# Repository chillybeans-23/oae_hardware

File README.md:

# OAE Hardware

probe_tip branch includes probe nozzle PCB, as well as chassis CAD

## Bill of Materials

[TODO]
* Speakers
* Microphone
* 34AWG magnet wire
* 0402? components
* PCBs
* EEPROM chips
* HDMI cable
* Assorted heatshrink tubing
* 

## Assembly Instructions

The optimal location to assemble the probe is in the EE Proto Room. Here, you can find the necessary equipment to assemble the probe:

* Weller soldering station, with fine point iron tip
* Fine gauge lead-free solder wire
* No-clean flux
* Helping hands with silicone, with rubber alligator clip covers
* Silicone soldering pad
* Mounting putty (poster putty)
* Hotplate
* Tweezers
* Wire strippers
* Exacto knife
* Multimeter

### Step 1: Assemble the PCB

The nozzle PCB contains the Microchip 24LC32A I2C compatible serial EEPROM, its auxiliary components, and pads to solder HDMI and magnet wire to. To assemble the components before hand-soldering the magnet wire and HDMI cable, follow these instructions, and refer to Bradley Minch for use of his hotplate or expertise:

**Instructions for solder application**

[TODO] assemble another PCB and take pictures for each step

1. Lay PCB on silicone or other flat surface with IC/component side upwards
2. Lay stencil over PCB, ensuring the component pads line up
3. Carefully align stencil on top of PCB and hold down firmly
4. Applying tension, tape opposite corners of stencil to the work surface
5. Repeat for the other two corners of the stencil
6. Ensure the component pads still line up with the stencil cutouts, and the PCB is held securely in place
7. Mix the solder paste evenly
8. Apply a rice grain size amount of solder paste to the stencil next to the cutouts
9. Applying moderate pressure with the squeegee at a 30 degree angle with the surface, drag the solder paste along the stencil into the cutouts
10. Drag the solder paste the other way
11. Repeat 1-2 times until all the cutouts are full of solder paste
12. Using the squeegee, scrape the excess solder paste off the stencil
13. Scrape the excess solder paste off the squeegee back into the container
14. Untape the stencil from the work surface
15. Ensure there is an even layer of solder paste on the pads of the PCB
16. Using isopropyl alcohol and a Kimwipe, clean the squeegee and stencil

**Instructions for Populating the PCB**

1. Refer to the interactive Bill of Materials (BOM) for component values and locations [TODO]
2. Cut one 1uF capacitor and two 2k resistors off their respective tapes
3. Use angled tweezers to place the components
    * Getting one tweezer prong slightly sticky and just using that prong to place is better than pinching the components
    * Place hand on table close to PCB for stability
    * The specified capacitors and resistors have no polarity and can be placed with any side up, as long as the component lays flat along the PCB

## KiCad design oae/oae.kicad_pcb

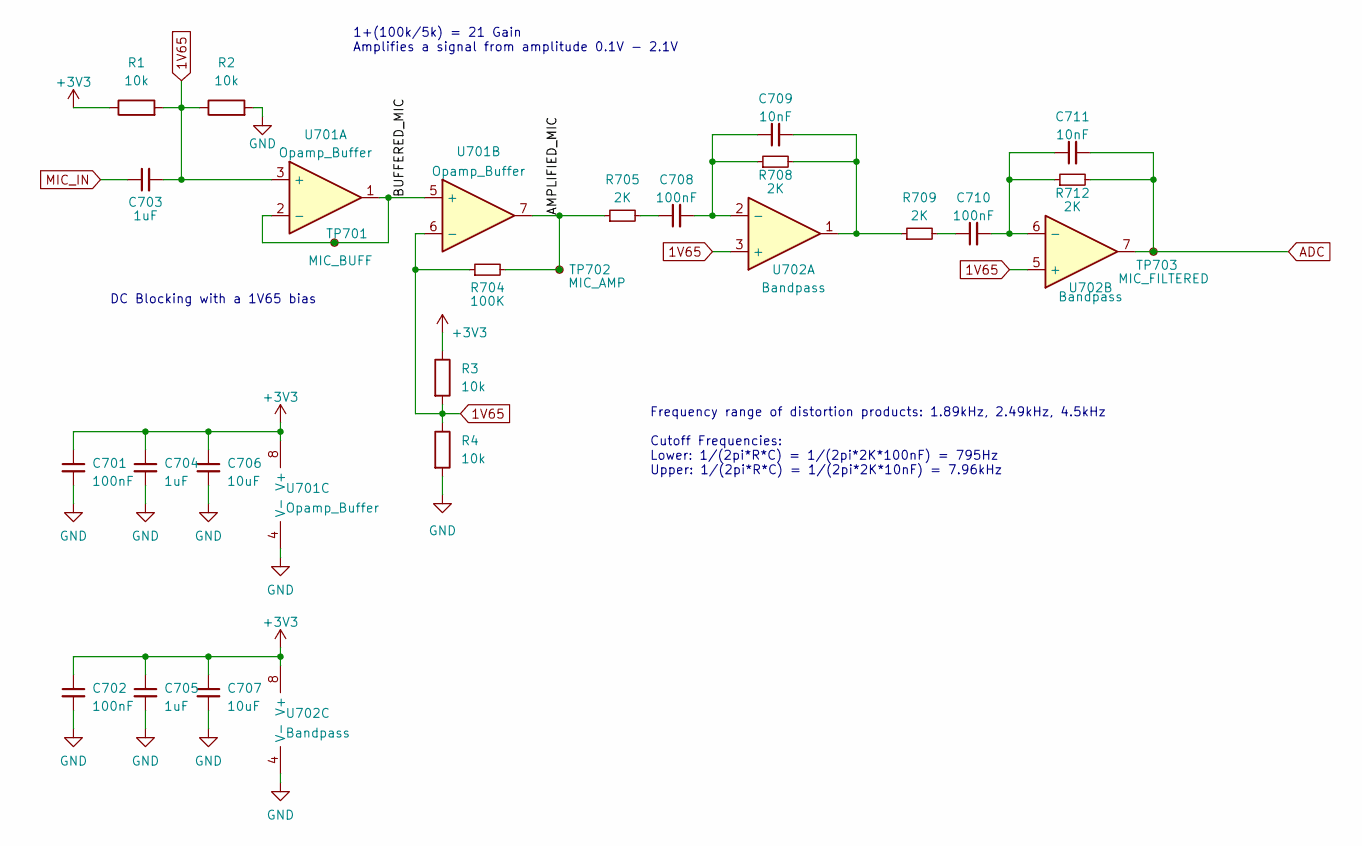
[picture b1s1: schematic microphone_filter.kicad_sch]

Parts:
C701, C702: 100nF; C_0603_1608Metric
C703: 1uF; C_1206_3216Metric_Pad1.33x1.80mm_HandSolder
C704, C705: 1uF; C_0603_1608Metric
C706, C707: 10uF; C_0603_1608Metric
C708, C710: 100nF; C_1206_3216Metric
C709, C711: 10nF; C_0603_1608Metric
R1, R2, R3, R4: 10k; R_0603_1608Metric
R704: 100K; R_0603_1608Metric_Pad0.98x0.95mm_HandSolder
R705, R708, R709, R712: 2K; R_0603_1608Metric_Pad0.98x0.95mm_HandSolder
TP701: MIC_BUFF; TestPoint_Pad_D2.5mm
TP702: MIC_AMP; TestPoint_Pad_D2.5mm
TP703: MIC_FILTERED; TestPoint_Pad_D2.5mm
U1: PCM1862DBT; C_0603_1608Metric
U701: Opamp_Buffer; SOIC127P599X175-8N; Digikey MCP6022-I/SN-ND
U702: Bandpass; SOIC127P599X175-8N; Digikey MCP6022-I/SN-ND

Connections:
/Microphone Filters and Amp/AMPLIFIED_MIC: R704.2, R705.1, TP702.1, U701.7
/Microphone Filters and Amp/BUFFERED_MIC: TP701.1, U701.1, U701.2 (-), U701.5 (+)
ADC: C711.2, R712.2, TP703.1, U702.7; also elsewhere on the board
MIC_IN: C703.1; also elsewhere on the board
unnamed: C708.1, R705.2
unnamed: C709.2, R708.2, R709.1, U702.1
unnamed: C710.1, R709.2
unnamed: C708.2, C709.1, R708.1, U702.2 (-)
unnamed: C710.2, C711.1, R712.1, U702.6 (-)

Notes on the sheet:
1+(100k/5k) = 21 Gain Amplifies a signal from amplitude 0.1V - 2.1V
DC Blocking with a 1V65 bias
Frequency range of distortion products: 1.89kHz, 2.49kHz, 4.5kHz Cutoff Frequencies: Lower: 1/(2pi*R*C) = 1/(2pi*2K*100nF) = 795Hz Upper: 1/(2pi*R*C) = 1/(2pi*2K*10nF) = 7.96kHz

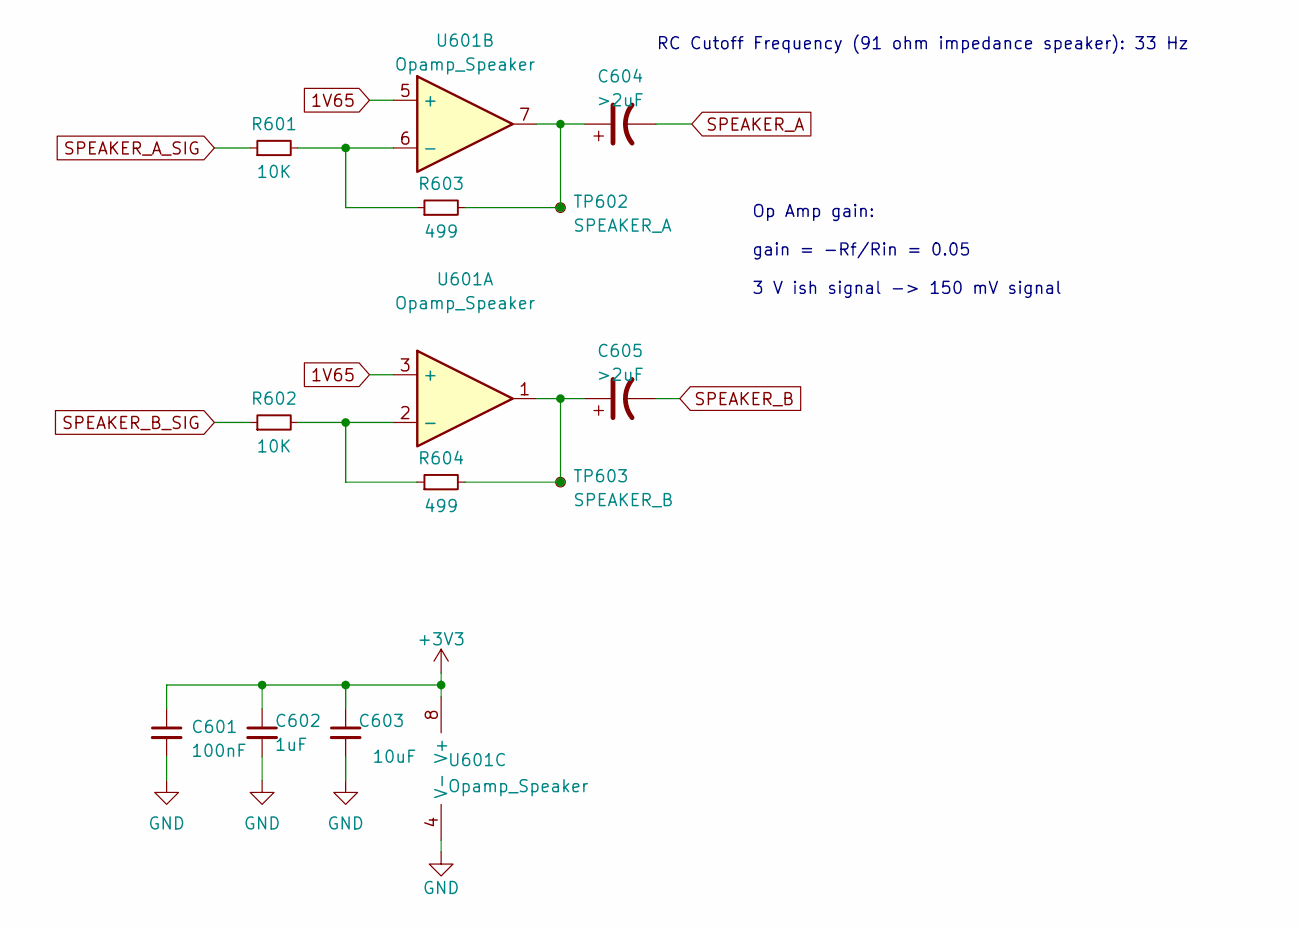
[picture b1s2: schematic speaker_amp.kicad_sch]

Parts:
C601: 100nF; C_0603_1608Metric
C602: 1uF; C_0603_1608Metric
C603: 10uF; C_0603_1608Metric
C604, C605: >2uF; C_0805_2012Metric_Pad1.18x1.45mm_HandSolder
R601, R602: 10K; R_0603_1608Metric_Pad0.98x0.95mm_HandSolder
R603, R604: 499; R_0603_1608Metric_Pad0.98x0.95mm_HandSolder
TP602: SPEAKER_A; TestPoint_Pad_D2.5mm
TP603: SPEAKER_B; TestPoint_Pad_D2.5mm
U601: Opamp_Speaker; SOIC127P599X175-8N; Digikey MCP6022-I/SN-ND

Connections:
unnamed: C604.1, R603.2, TP602.1, U601.7
unnamed: C605.1, R604.2, TP603.1, U601.1
unnamed: R602.2, R604.1, U601.2 (-)
unnamed: R601.2, R603.1, U601.6 (-)
SPEAKER_A: C604.2; also elsewhere on the board
SPEAKER_A_SIG: R601.1; also elsewhere on the board
SPEAKER_B: C605.2; also elsewhere on the board
SPEAKER_B_SIG: R602.1; also elsewhere on the board

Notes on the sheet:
Op Amp gain: gain = -Rf/Rin = 0.05 3 V ish signal -> 150 mV signal
RC Cutoff Frequency (91 ohm impedance speaker): 33 Hz

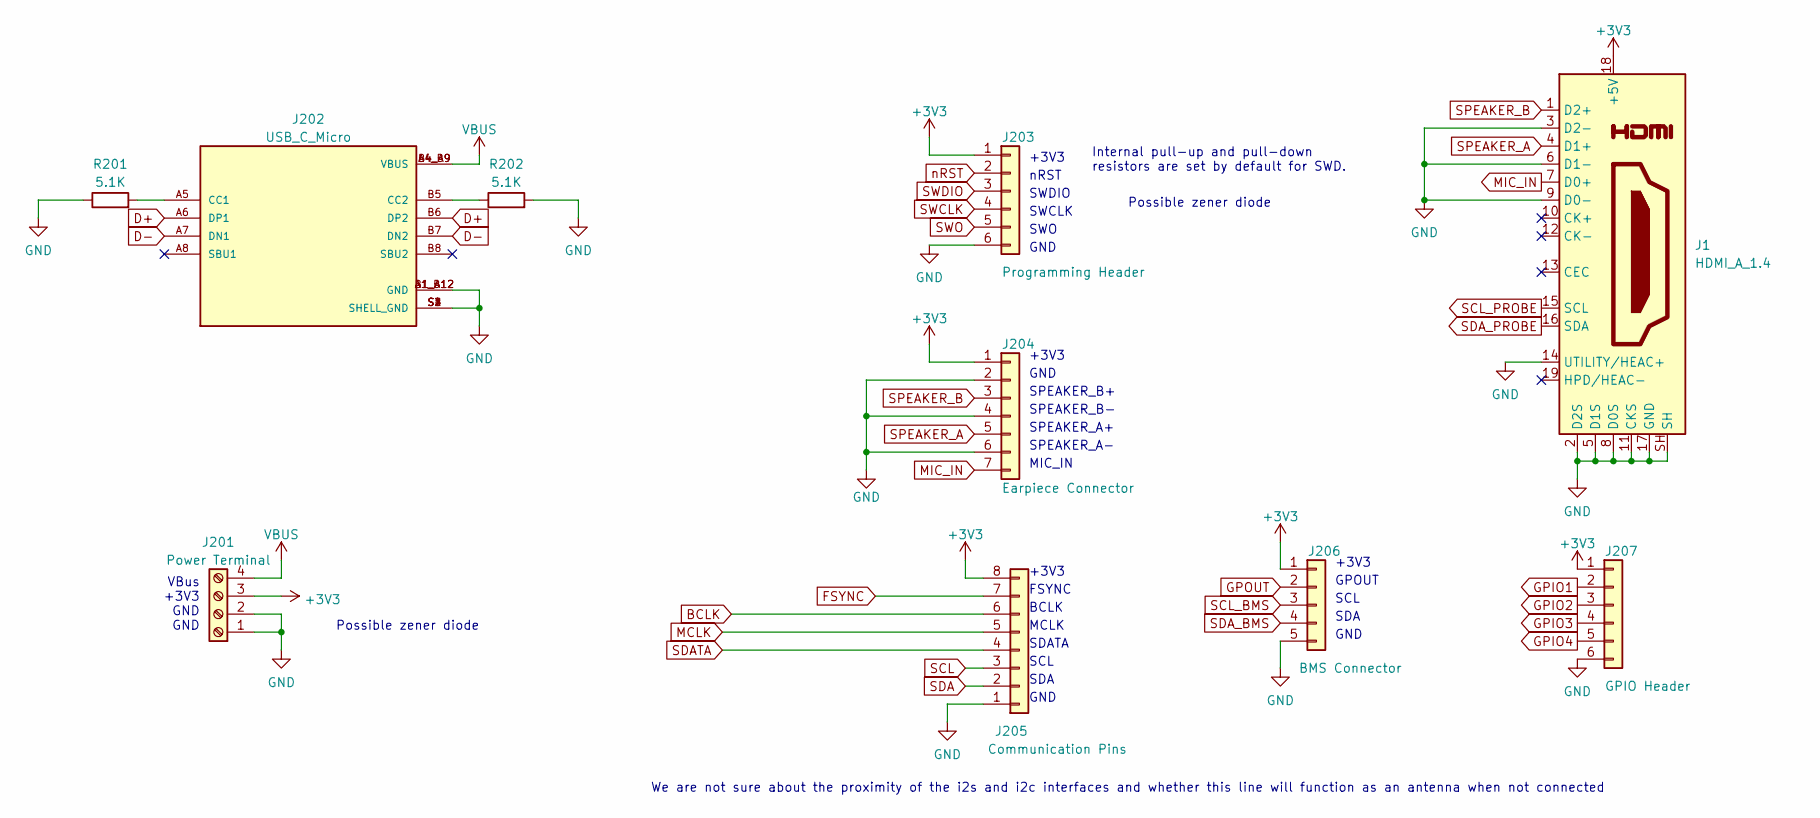
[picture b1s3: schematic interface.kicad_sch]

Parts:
J1: HDMI_A_1.4; HDMI_A_Molex_208658-1001_Horizontal
J201: Power Terminal; PinHeader_1x04_P2.54mm_Vertical
J202: USB_C_Micro; GCT_USB4105-GF-A; PARTREV A3
J203: Programming Header; PinHeader_1x06_P2.54mm_Vertical
J204: Earpiece Connector; PinHeader_1x07_P2.54mm_Vertical
J205: Communication Pins; PinHeader_1x08_P2.54mm_Vertical
J206: BMS Connector; PinHeader_1x05_P2.54mm_Vertical
J207: GPIO Header; PinHeader_1x06_P2.54mm_Vertical
R201, R202: 5.1K; R_0603_1608Metric_Pad0.98x0.95mm_HandSolder

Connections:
BCLK: J205.6; also elsewhere on the board
D+: J202.A6 (DP1), J202.B6 (DP2); also elsewhere on the board
D-: J202.A7 (DN1), J202.B7 (DN2); also elsewhere on the board
FSYNC: J205.7; also elsewhere on the board
GPIO1: J207.2; also elsewhere on the board
GPIO2: J207.3; also elsewhere on the board
GPIO3: J207.4; also elsewhere on the board
GPIO4: J207.5; also elsewhere on the board
GPOUT: J206.2; also elsewhere on the board
MCLK: J205.5; also elsewhere on the board
MIC_IN: J1.7 (D0+), J204.7; also elsewhere on the board
unnamed: J202.A5 (CC1), R201.2
unnamed: J202.B5 (CC2), R202.1
SCL: J205.3; also elsewhere on the board
SCL_BMS: J206.3; also elsewhere on the board
SCL_PROBE: J1.15 (SCL); also elsewhere on the board
SDA: J205.2; also elsewhere on the board
SDATA: J205.4; also elsewhere on the board
SDA_BMS: J206.4; also elsewhere on the board
SDA_PROBE: J1.16 (SDA); also elsewhere on the board
SPEAKER_A: J1.4 (D1+), J204.5; also elsewhere on the board
SPEAKER_B: J1.1 (D2+), J204.3; also elsewhere on the board
SWCLK: J203.4; also elsewhere on the board
SWDIO: J203.3; also elsewhere on the board
SWO: J203.5; also elsewhere on the board
VBUS: J201.4, J202.A4_B9 (VBUS), J202.B4_A9 (VBUS); also elsewhere on the board
nRST: J203.2; also elsewhere on the board

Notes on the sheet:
SPEAKER_B-
SWO
MIC_IN
GND
VBus +3V3 GND GND
MCLK
nRST
SPEAKER_A+
+3V3
FSYNC
SCL
GPOUT
Internal pull-up and pull-down resistors are set by default for SWD.
Possible zener diode
We are not sure about the proximity of the i2s and i2c interfaces and whether this line will function as an antenna when not connected
SWCLK
SDA
SPEAKER_A-
SWDIO
BCLK
SPEAKER_B+
SDATA
SCL

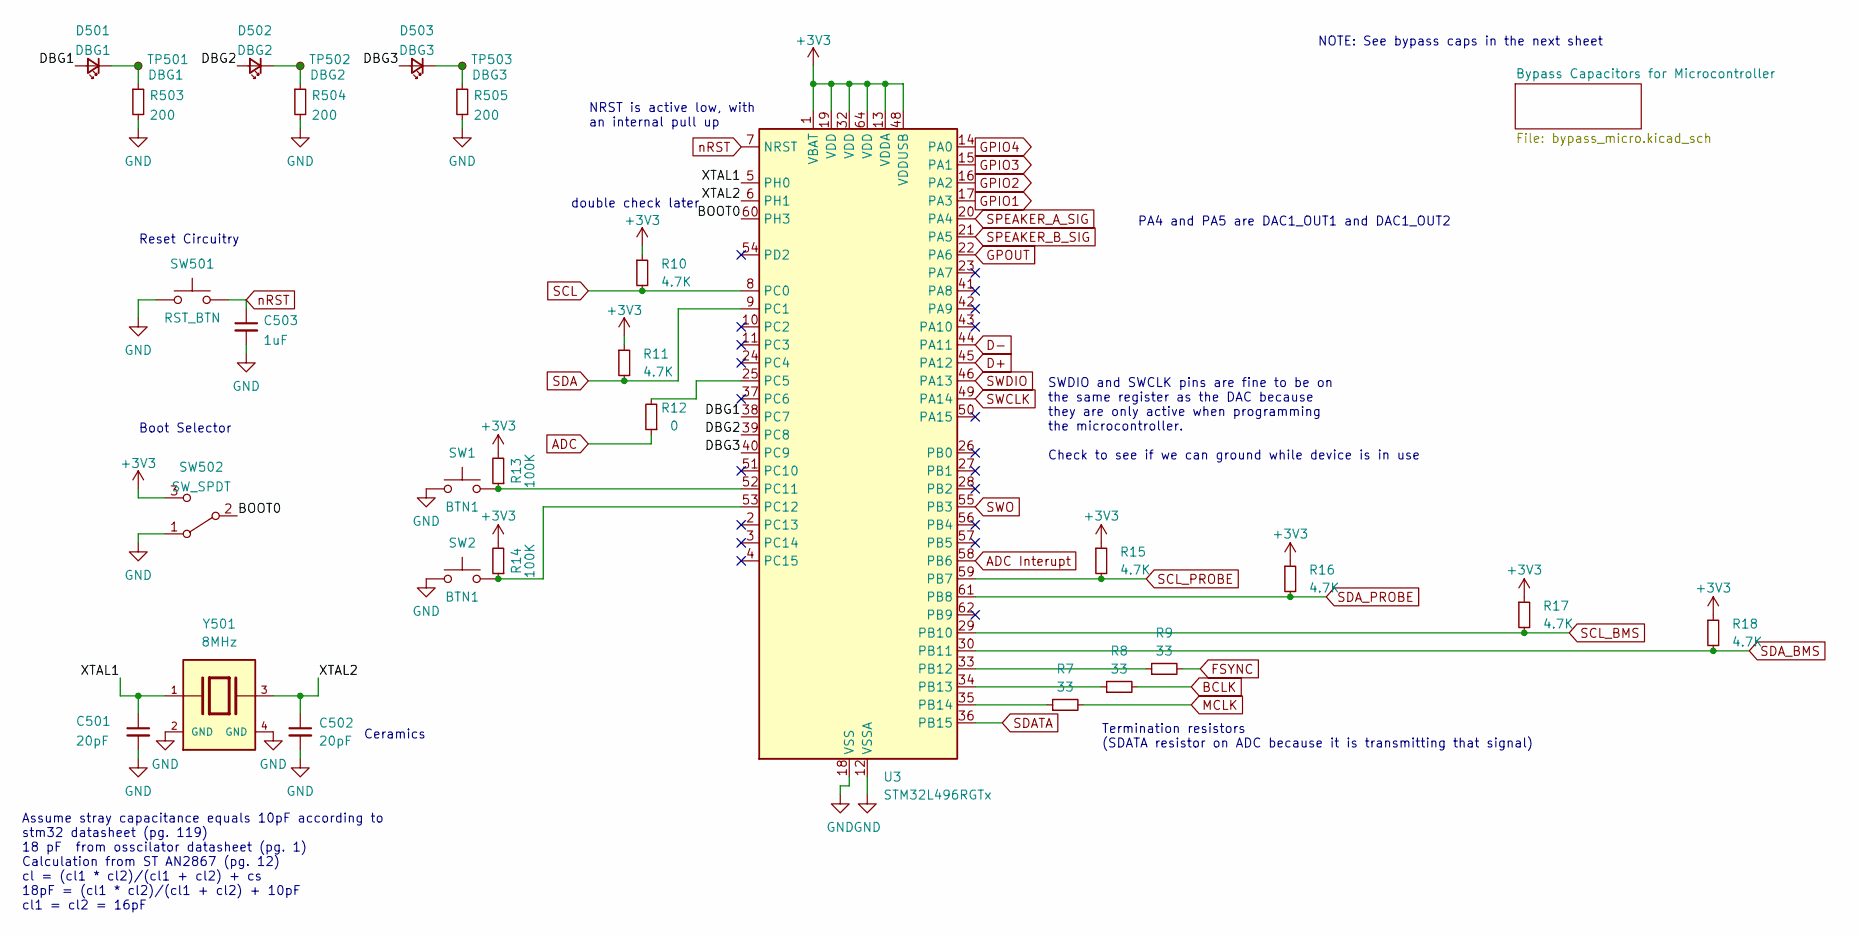
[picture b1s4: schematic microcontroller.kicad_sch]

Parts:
C501, C502: 20pF; C_0603_1608Metric
C503: 1uF; C_0603_1608Metric
D501: DBG1; LED_0603_1608Metric
D502: DBG2; LED_0603_1608Metric
D503: DBG3; LED_0603_1608Metric
R7, R8, R9: 33; R_0603_1608Metric_Pad0.98x0.95mm_HandSolder
R10, R11, R15, R16, R17, R18: 4.7K; R_0603_1608Metric_Pad0.98x0.95mm_HandSolder
R12: 0; R_0603_1608Metric_Pad0.98x0.95mm_HandSolder
R13, R14: 100K; R_0603_1608Metric_Pad0.98x0.95mm_HandSolder
R503, R504, R505: 200; R_0603_1608Metric_Pad0.98x0.95mm_HandSolder
SW1, SW2: BTN1; SW_SPST_EVPBF; DigiKey P19749DKR-ND
SW501: RST_BTN; SW_SPST_EVPBF; DigiKey P19749DKR-ND
SW502: SW_SPDT; PinHeader_1x03_P2.54mm_Vertical
TP501: DBG1; TestPoint_Pad_1.5x1.5mm
TP502: DBG2; TestPoint_Pad_1.5x1.5mm
TP503: DBG3; TestPoint_Pad_1.5x1.5mm
U3: STM32L496RGTx; LQFP-64_10x10mm_P0.5mm
Y501: 8MHz; XTAL_ABMM2-8.000MHZ-E2-T; PARTREV 01.18.13

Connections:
/Microcontroller/BOOT0: SW502.2 (B), U3.60 (PH3)
/Microcontroller/DBG1: D501.2 (A), U3.38 (PC7)
/Microcontroller/DBG2: D502.2 (A), U3.39 (PC8)
/Microcontroller/DBG3: D503.2 (A), U3.40 (PC9)
/Microcontroller/XTAL1: C501.1, U3.5 (PH0), Y501.1
/Microcontroller/XTAL2: C502.1, U3.6 (PH1), Y501.3
ADC: R12.1; also elsewhere on the board
ADC Interupt: U3.58 (PB6); also elsewhere on the board
BCLK: R8.2; also elsewhere on the board
D+: U3.45 (PA12); also elsewhere on the board
D-: U3.44 (PA11); also elsewhere on the board
FSYNC: R9.2; also elsewhere on the board
GPIO1: U3.17 (PA3); also elsewhere on the board
GPIO2: U3.16 (PA2); also elsewhere on the board
GPIO3: U3.15 (PA1); also elsewhere on the board
GPIO4: U3.14 (PA0); also elsewhere on the board
GPOUT: U3.22 (PA6); also elsewhere on the board
MCLK: R7.2; also elsewhere on the board
unnamed: D501.1 (K), R503.1, TP501.1
unnamed: D502.1 (K), R504.1, TP502.1
unnamed: D503.1 (K), R505.1, TP503.1
unnamed: R9.1, U3.33 (PB12)
unnamed: R8.1, U3.34 (PB13)
unnamed: R7.1, U3.35 (PB14)
unnamed: R12.2, U3.25 (PC5)
unnamed: R13.1, SW1.2, U3.52 (PC11)
unnamed: R14.1, SW2.2, U3.53 (PC12)
SCL: R10.2, U3.8 (PC0); also elsewhere on the board
SCL_BMS: R17.2, U3.29 (PB10); also elsewhere on the board
SCL_PROBE: R15.2, U3.59 (PB7); also elsewhere on the board
SDA: R11.2, U3.9 (PC1); also elsewhere on the board
SDATA: U3.36 (PB15); also elsewhere on the board
SDA_BMS: R18.2, U3.30 (PB11); also elsewhere on the board
SDA_PROBE: R16.2, U3.61 (PB8); also elsewhere on the board
SPEAKER_A_SIG: U3.20 (PA4); also elsewhere on the board
SPEAKER_B_SIG: U3.21 (PA5); also elsewhere on the board
SWCLK: U3.49 (PA14); also elsewhere on the board
SWDIO: U3.46 (PA13); also elsewhere on the board
SWO: U3.55 (PB3); also elsewhere on the board
nRST: C503.1, SW501.2, U3.7 (NRST); also elsewhere on the board

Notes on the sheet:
Ceramics
Termination resistors (SDATA resistor on ADC because it is transmitting that signal)
Reset Circuitry
Boot Selector
NRST is active low, with an internal pull up
Assume stray capacitance equals 10pF according to stm32 datasheet (pg. 119) 18 pF from osscilator datasheet (pg. 1) Calculation from ST AN2867 (pg. 12) cl = (cl1 * cl2)/(cl1 + cl2) + cs 18pF = (cl1 * cl2)/(cl1 + cl2) + 10pF cl1 = cl2 = 16pF
double check later
NOTE: See bypass caps in the next sheet
PA4 and PA5 are DAC1_OUT1 and DAC1_OUT2
SWDIO and SWCLK pins are fine to be on the same register as the DAC because they are only active when programming the microcontroller. Check to see if we can ground while device is in use

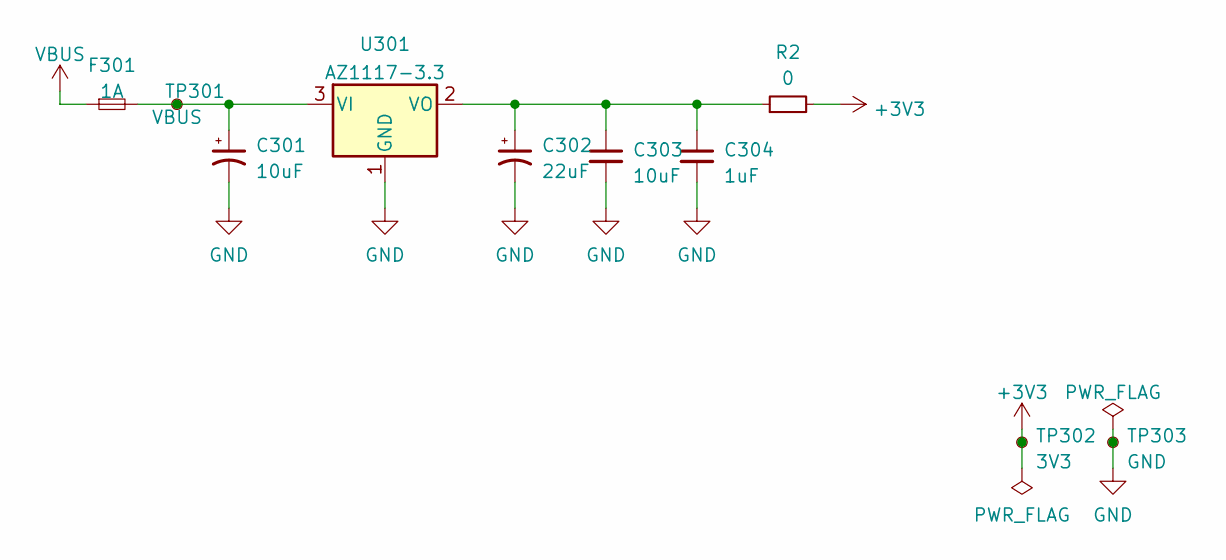
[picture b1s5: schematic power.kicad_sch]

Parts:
C301, C303: 10uF; C_0603_1608Metric
C302: 22uF; C_0603_1608Metric
C304: 1uF; C_0603_1608Metric
F301: 1A; Fuse_1206_3216Metric; DigiKey 507-1806-6-ND
R2: 0; R_0603_1608Metric_Pad0.98x0.95mm_HandSolder
TP301: VBUS; TestPoint_Pad_D2.5mm
TP302: 3V3; TestPoint_Pad_D2.5mm
TP303: GND; TestPoint_Pad_D2.5mm
U301: AZ1117-3.3; TO-252-3_TabPin2; DigiKey AZ1117CD-3.3TRG1DIDKR-ND

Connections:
unnamed: C301.1, F301.2, TP301.1, U301.3 (VI)
VBUS: F301.1; also elsewhere on the board

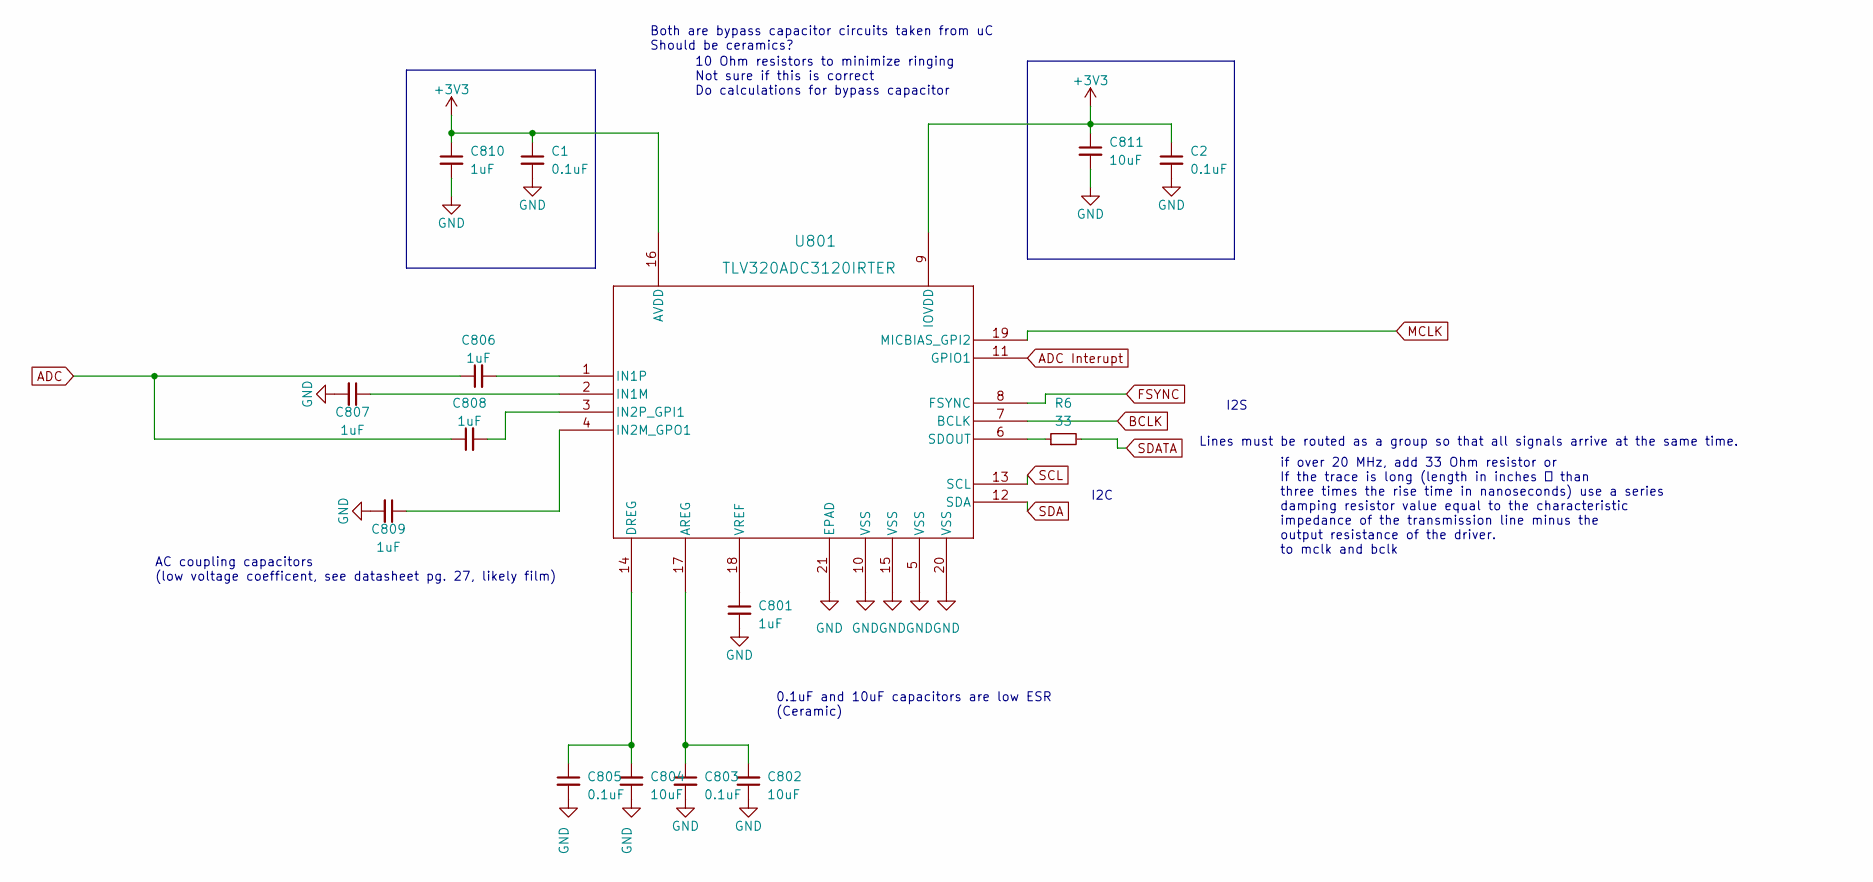
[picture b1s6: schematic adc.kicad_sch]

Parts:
C1, C2, C803, C805: 0.1uF; C_0603_1608Metric
C801, C810: 1uF; C_0603_1608Metric
C802, C804, C811: 10uF; C_0603_1608Metric
C806, C807, C808, C809: 1uF; C_1206_3216Metric_Pad1.33x1.80mm_HandSolder
R6: 33; R_0603_1608Metric_Pad0.98x0.95mm_HandSolder
U801: TLV320ADC3120IRTER; WQFN20_RTE_TEX

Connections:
ADC: C806.1, C808.1; also elsewhere on the board
ADC Interupt: U801.11 (GPIO1); also elsewhere on the board
BCLK: U801.7 (BCLK); also elsewhere on the board
FSYNC: U801.8 (FSYNC); also elsewhere on the board
MCLK: U801.19 (MICBIAS_GPI2); also elsewhere on the board
unnamed: C802.2, C803.1, U801.17 (AREG)
unnamed: C804.2, C805.1, U801.14 (DREG)
unnamed: C807.1, U801.2 (IN1M)
unnamed: C806.2, U801.1 (IN1P)
unnamed: C809.1, U801.4 (IN2M_GPO1)
unnamed: C808.2, U801.3 (IN2P_GPI1)
unnamed: R6.1, U801.6 (SDOUT)
unnamed: C801.1, U801.18 (VREF)
SCL: U801.13 (SCL); also elsewhere on the board
SDA: U801.12 (SDA); also elsewhere on the board
SDATA: R6.2; also elsewhere on the board

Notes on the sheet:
AC coupling capacitors (low voltage coefficent, see datasheet pg. 27, likely film)
I2C
10 Ohm resistors to minimize ringing Not sure if this is correct Do calculations for bypass capacitor
0.1uF and 10uF capacitors are low ESR (Ceramic)
if over 20 MHz, add 33 Ohm resistor or If the trace is long (length in inches  than three times the rise time in nanoseconds) use a series damping resistor value equal to the characteristic impedance of the transmission line minus the output resistance of the driver. to mclk and bclk
I2S
Lines must be routed as a group so that all signals arrive at the same time.
Both are bypass capacitor circuits taken from uC Should be ceramics?

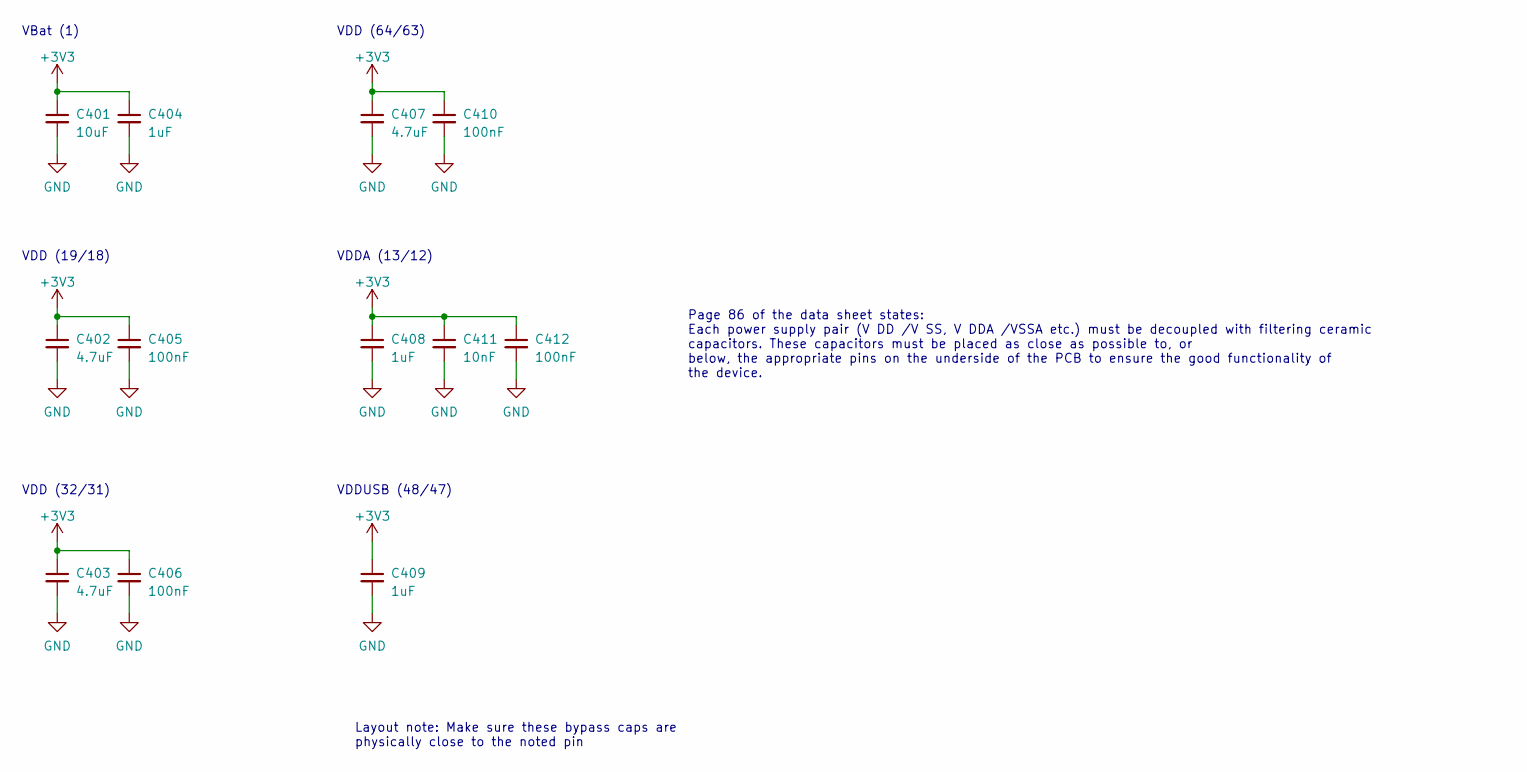
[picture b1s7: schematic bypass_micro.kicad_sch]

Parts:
C401: 10uF; C_0603_1608Metric
C402, C403, C407: 4.7uF; C_0603_1608Metric
C404, C408, C409: 1uF; C_0603_1608Metric
C405, C406, C410, C412: 100nF; C_0603_1608Metric
C411: 10nF; C_0603_1608Metric

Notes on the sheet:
VBat (1)
VDD (64/63)
Layout note: Make sure these bypass caps are physically close to the noted pin
VDD (32/31)
VDD (19/18)
VDDA (13/12)
Page 86 of the data sheet states: Each power supply pair (V DD /V SS, V DDA /VSSA etc.) must be decoupled with filtering ceramic capacitors. These capacitors must be placed as close as possible to, or below, the appropriate pins on the underside of the PCB to ensure the good functionality of the de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
VDDUSB (48/47)

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
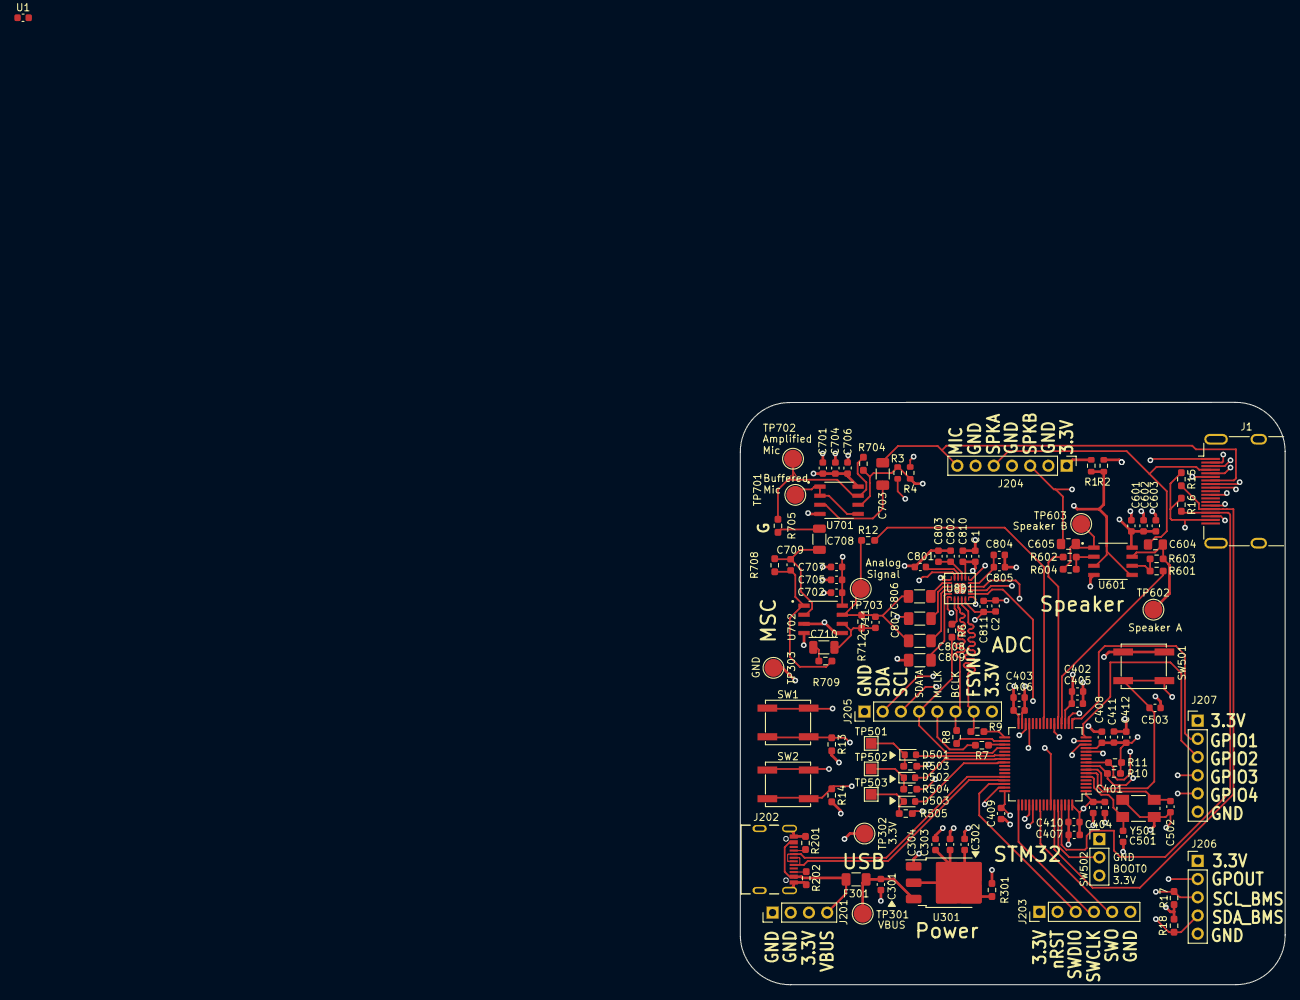
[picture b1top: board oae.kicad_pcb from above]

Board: 4 copper layers, 76.0 x 81.2 mm, 115 parts (0 on the bottom side), 70 nets.

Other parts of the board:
R301: 0; R_0603_1608Metric_Pad0.98x0.95mm_HandSolder

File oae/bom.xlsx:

Id | Designator | Footprint | Quantity | Comment | Supplier and ref
1 | TP302 | TestPoint_Pad_D2.5mm | 1 | 3V3
2 | C304,C704,C404,C408,C801,C409,C503,C810,C705,C602 | C_0603_1608Metric | 10 | 1uF
3 | C702,C601,C405,C406,C410,C701,C412 | C_0603_1608Metric | 7 | 100nF
4 | J206 | PinHeader_1x05_P2.54mm_Vertical | 1 | BMS Connector
5 | C804,C301,C706,C811,C603,C303,C802,C707,C401 | C_0603_1608Metric | 9 | 10uF
6 | TP701 | TestPoint_Pad_D2.5mm | 1 | MIC_BUFF
7 | R504,R503,R505 | R_0603_1608Metric_Pad0.98x0.95mm_HandSolder | 3 | 200
8 | R201,R202 | R_0603_1608Metric_Pad0.98x0.95mm_HandSolder | 2 | 5.1K
9 | J207 | PinHeader_1x06_P2.54mm_Vertical | 1 | GPIO Header
10 | R604,R603 | R_0603_1608Metric_Pad0.98x0.95mm_HandSolder | 2 | 499
11 | C605,C604 | C_0805_2012Metric_Pad1.18x1.45mm_HandSolder | 2 | >2uF
12 | R708,R709,R705,R712 | R_0603_1608Metric_Pad0.98x0.95mm_HandSolder | 4 | 2K
13 | TP502 | TestPoint_Pad_1.5x1.5mm | 1 | DBG2
14 | C708,C710 | C_0805_2012Metric_Pad1.18x1.45mm_HandSolder | 2 | 100nF
15 | RN3,RN1,RN2 | R_Array_Convex_2x0603 | 3 | 10K
16 | C2,C803,C805,C1 | C_0603_1608Metric | 4 | 0.1uF
17 | TP603 | TestPoint_Pad_D2.5mm | 1 | SPEAKER_B
18 | C502,C501 | C_0603_1608Metric | 2 | 16pF
19 | R301,R12 | R_0603_1608Metric_Pad0.98x0.95mm_HandSolder | 2 | 0
20 | TP303 | TestPoint_Pad_D2.5mm | 1 | GND
21 | R17,R10,R15,R16,R11,R18 | R_0603_1608Metric_Pad0.98x0.95mm_HandSolder | 6 | 4.7K
22 | J202 | GCT_USB4105-GF-A | 1 | USB_C_Micro
23 | J201 | PinHeader_1x04_P2.54mm_Vertical | 1 | Power Terminal
24 | SW2,SW1 | SW_SPST_EVPBF | 2 | BTN1
25 | TP501 | TestPoint_Pad_1.5x1.5mm | 1 | DBG1
26 | R704,R14,R13 | R_0603_1608Metric_Pad0.98x0.95mm_HandSolder | 3 | 100K
27 | F301 | Fuse_1206_3216Metric | 1 | 1A
28 | J204 | PinHeader_1x07_P2.54mm_Vertical | 1 | Earpiece Connector
29 | D503 | LED_0603_1608Metric | 1 | DBG3
30 | TP301 | TestPoint_Pad_D2.5mm | 1 | VBUS
31 | C809,C703,C806,C808,C807 | C_1206_3216Metric_Pad1.33x1.80mm_HandSolder | 5 | 1uF
32 | R9,R7,R8,R6 | R_0603_1608Metric_Pad0.98x0.95mm_HandSolder | 4 | 33
33 | SW501 | SW_SPST_EVPBF | 1 | RST_BTN
34 | U701 | SOIC127P599X175-8N | 1 | Opamp_Buffer
35 | J203 | PinHeader_1x06_P2.54mm_Vertical | 1 | Programming Header
36 | R602,R601 | R_0603_1608Metric_Pad0.98x0.95mm_HandSolder | 2 | 10K
37 | TP601 | TestPoint_Pad_D2.5mm | 1 | 1V65
38 | C302 | C_0603_1608Metric | 1 | 22uF
39 | TP703 | TestPoint_Pad_D2.5mm | 1 | MIC_FILTERED
40 | C711,C709 | C_0805_2012Metric_Pad1.18x1.45mm_HandSolder | 2 | 10nF
41 | TP503 | TestPoint_Pad_1.5x1.5mm | 1 | DBG3
42 | C411 | C_0603_1608Metric | 1 | 10nF
43 | Y501 | XTAL_ABMM2-8.000MHZ-E2-T | 1 | 8MHz
44 | U702 | SOIC127P599X175-8N | 1 | Bandpass
45 | U3 | LQFP-64_10x10mm_P0.5mm | 1 | STM32L496RGTx
46 | C402,C407,C403 | C_0603_1608Metric | 3 | 4.7uF
47 | SW502 | PinHeader_1x03_P2.54mm_Vertical | 1 | SW_SPDT
48 | U601 | SOIC127P599X175-8N | 1 | Opamp_Speaker
49 | TP602 | TestPoint_Pad_D2.5mm | 1 | SPEAKER_A
50 | U301 | TO-252-3_TabPin2 | 1 | AZ1117-3.3
51 | D502 | LED_0603_1608Metric | 1 | DBG2
52 | U801 | WQFN20_RTE_TEX | 1 | TLV320ADC3120IRTER
53 | D501 | LED_0603_1608Metric | 1 | DBG1
54 | J205 | PinHeader_1x08_P2.54mm_Vertical | 1 | Communication Pins
55 | TP702 | TestPoint_Pad_D2.5mm | 1 | MIC_AMP
56 | J1 | HDMI_A_Molex_208658-1001_Horizontal | 1 | HDMI_A_1.4

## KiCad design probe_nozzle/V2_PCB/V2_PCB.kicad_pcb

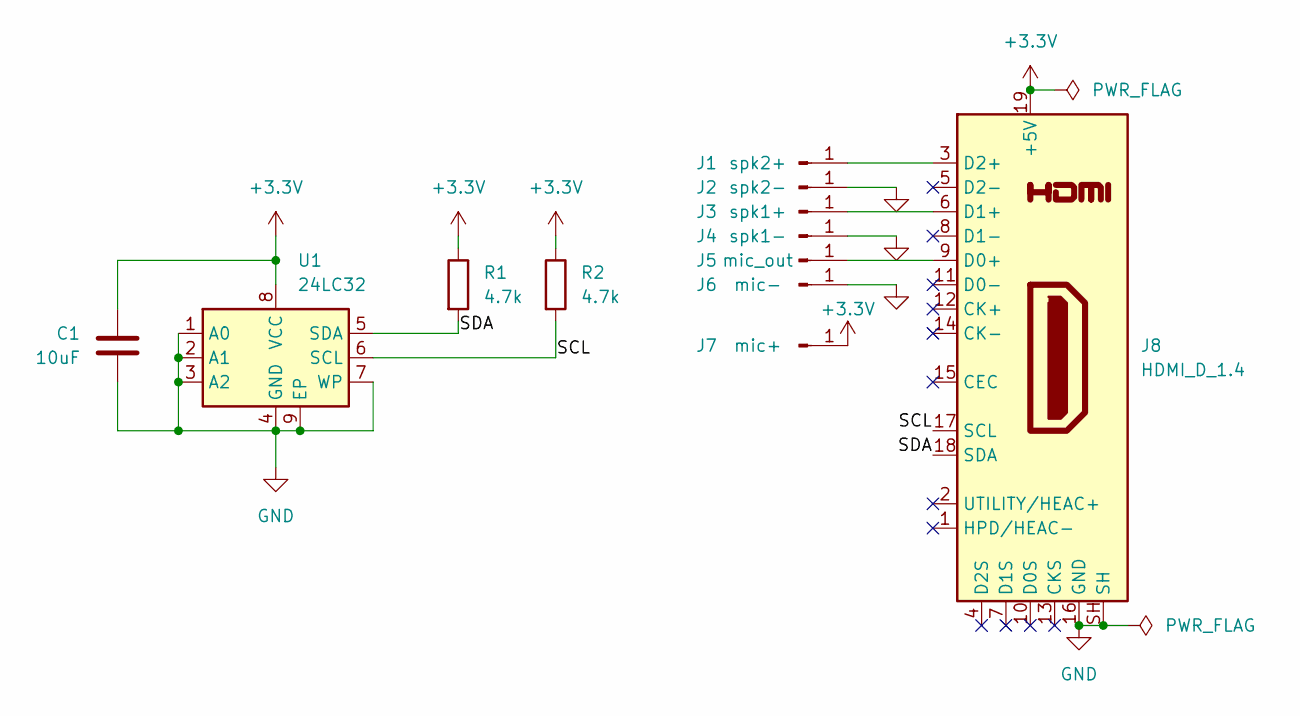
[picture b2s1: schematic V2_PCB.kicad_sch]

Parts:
C1: 10uF; C_0402_1005Metric_Pad0.74x0.62mm_HandSolder
J1: spk2+; 1x1mm_Pad
J2: spk2-; 1x1mm_Pad
J3: spk1+; 1x1mm_Pad
J4: spk1-; 1x1mm_Pad
J5: mic_out; 1x1mm_Pad
J6: mic-; 1x1mm_Pad
J7: mic+; 1x1mm_Pad
J8: HDMI_D_1.4; HDMI_Micro-D_Molex_46765-1x01
R1, R2: 4.7k; R_0402_1005Metric_Pad0.72x0.64mm_HandSolder
U1: 24LC32; DFN8_2x3MC_MCH-L

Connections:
+3.3V: C1.2, J7.1, J8.19 (+5V), R1.1, R2.1, U1.8 (VCC)
/SCL: J8.17 (SCL), R2.2, U1.6 (SCL)
/SDA: J8.18 (SDA), R1.2, U1.5 (SDA)
GND: C1.1, J2.1, J4.1, J6.1, J8.16 (GND), J8.SH, U1.1 (A0), U1.2 (A1), U1.3 (A2), U1.4 (GND), U1.7 (WP), U1.9 (EP)
unnamed: J1.1, J8.3 (D2+)
unnamed: J3.1, J8.6 (D1+)
unnamed: J5.1, J8.9 (D0+)

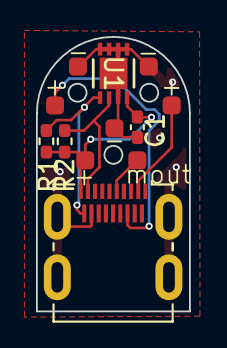
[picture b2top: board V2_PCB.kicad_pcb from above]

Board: 2 copper layers, 8.5 x 15.2 mm, 12 parts (0 on the bottom side), 7 nets.

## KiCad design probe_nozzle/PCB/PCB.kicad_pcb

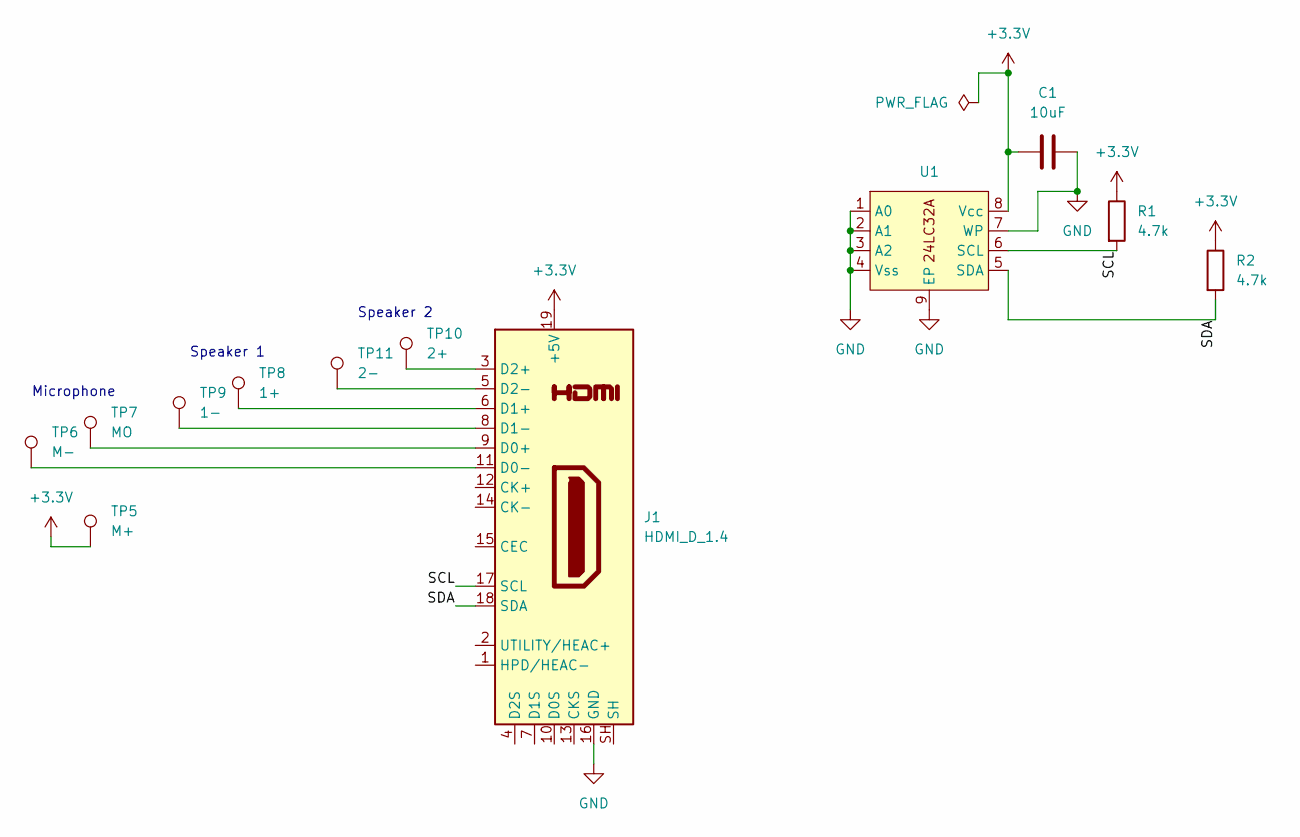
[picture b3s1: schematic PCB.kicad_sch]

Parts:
C1: 10uF; C_0402_1005Metric
J1: HDMI_D_1.4; 46765-1001_MOL
R1, R2: 4.7k; R_0402_1005Metric
TP5: M+; TestPoint_Pad_1.0x1.0mm
TP6: M-; TestPoint_Pad_1.0x1.0mm
TP7: MO; TestPoint_Pad_1.0x1.0mm
TP8: 1+; TestPoint_Pad_1.0x1.0mm
TP9: 1-; TestPoint_Pad_1.0x1.0mm
TP10: 2+; TestPoint_Pad_1.0x1.0mm
TP11: 2-; TestPoint_Pad_1.0x1.0mm
U1: DFN8_2x3MC_MCH-L

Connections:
+3.3V: C1.1, J1.19 (+5V), R1.1, R2.1, TP5.1, U1.8 (Vcc)
/SCL: J1.17 (SCL), R1.2, U1.6 (SCL)
/SDA: J1.18 (SDA), R2.2, U1.5 (SDA)
GND: C1.2, J1.16 (GND), U1.1 (A0), U1.2 (A1), U1.3 (A2), U1.4 (Vss), U1.7 (WP), U1.9 (EP)
unnamed: J1.9 (D0+), TP7.1
unnamed: J1.11 (D0-), TP6.1
unnamed: J1.6 (D1+), TP8.1
unnamed: J1.8 (D1-), TP9.1
unnamed: J1.3 (D2+), TP10.1
unnamed: J1.5 (D2-), TP11.1

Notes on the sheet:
Speaker 2
Speaker 1
Microphone

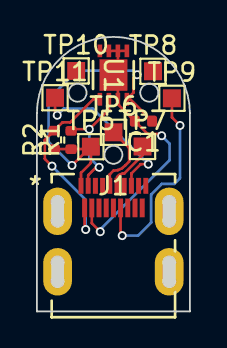
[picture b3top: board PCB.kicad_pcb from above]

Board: 2 copper layers, 8.5 x 15.2 mm, 12 parts (0 on the bottom side), 10 nets.
